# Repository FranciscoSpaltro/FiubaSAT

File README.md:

# Comunicación I2C

### Conexiones para la prueba con Arduino Nano

    1. GND (STM32) ---> GND (NANO)
    2. 5V  (STM32) ---> R_PULL_UP1 y R_PULL_UP2
    3. PB6 (STM32) ---> R_PULL_UP1 ---> PA5 (NANO) [SCL]
    4. PB7 (STM32) ---> R_PULL_UP2 ---> PA4 (NANO) [SDA]

### Protocolo para imprimir mensajes por Arduino via I2C
- Maestro (STM32): sin interrumpir la comunicación
    - Inicia la comunicación
    - Envía un comando a definir (IMPRIMIR_MENSAJE)
    - Envía la cadena caracteres sin interrumpir
    - Finaliza la comunicación
- Esclavo (ARDUINO):
    - Lee el comando
    - Recibe todos los bytes
    - Una vez finalizada la comunicacióon, imprime

### OBSERVACIONES
- FreeRTOS utiliza un contador de 32 bits para contar los ticks del sistema, lo que significa que se desbordará después de aproximadamente 49.7 días (para un sistema que corre a 1 ms por tick). Sin embargo, el cálculo de la diferencia, como en tu código, maneja correctamente el desbordamiento debido a la aritmética de enteros sin signo

### Próximos pasos
- Identificación de tipo de dato en el handshake? Vale la pena? El resto de los sensores no van a tener un micro
- Protección ante dirección de esclavo repetida
- Fallo en la conexión cableada se cuelga el I2C?
- En una falla que pasa con los mensajes que no se enviaron?
- Funciona bien la conexión entre hacer el rq (poner el mensaje en tx) y leer el dato (poner el mensaje en rx)? Es decir quien envia el dato puede trackear la respuesta?
- Investigar funcion i2c_write_restart de ve3wwg

- Tema memoria
- Si pido 5 bytes y me manda 1 que no se quede esperando después de un tiempo

### Comandos útiles RPi5
- pinout: muestra el pinout de la RPi
- gpiodetect: muestra los chips
- pinctrl: muestra info de todos los pines
- gpioinfo: muestra info de todos los pines por chip
- gpioget gpiochip0 4: muestra el estado del pin 4 del chip 0

### Tareas
- Rutina para chequeo de salud de los dispositivos
- Sacar los taskDelay, ver xTaskGetTickCount()
- ¿Mapa de esclavos por puerto? Y que decida por donde enviarlo (solo se necesitaría el slave_addr)

### Observaciones
- En los casos de reconexión/retransmisión, ver de combinar el taskYIELD() con un xTaskGetTickCount() para hacer que no vuelva a probar hasta que pase determinado tiempo
- Vale la pena las interrupciones?
- Revisar la variable global con la dirección del esclavo -> si hay más de un request como hago??
- La dirección 0x00 con el mensaje 0 está reservada para ERROR
- Función para leer?
- Revisar make_request, siempre hace get_i2c

### PROCESO DE TRANSMISION DE UN MENSAJE
1. Encolar un msg_t con la dirección y el dato a enviar en TXQ. El flag request debe estar en false
2. Iniciar la comunicación I2C en modo WRITE con i2c_start (puerto I2C, dirección del esclavo, false)
3. Enviar el byte de datos con i2c_write (puerto I2C, byte de datos)
4. Esperar a que se complete la transferencia de datos
5. Comprobar si se recibió ACK del esclavo
6. Enviar un STOP para finalizar la comunicación

### PROCESO DE SOLICITUD Y RECEPCIÓN DE UN MENSAJE
1. Encolar un msg_t con la dirección del esclavo en TXQ. El flag request debe estar en true
2. Iniciar la comunicación I2C en modo READ con i2c_start (puerto I2C, dirección del esclavo, true)
3. Leer el byte de datos con i2c_read (puerto I2C, true) y encolarlo en RXQ
4. Enviar un NACK si es el último byte a leer
5. Enviar un STOP para finalizar la comunicación

### FUNCIONES LIBOPENCM3
#### FUNCIONES DE CONFIGURACIÓN
1. i2c_peripheral_enable(uint32_t i2c): habilita el periférico I2C

2. i2c_peripheral_disable(uint32_t i2c): deshabilita el periférico I2C

3. i2c_set_own_7bit_slave_address(uint32_t i2c, uint8_t slave): configura la dirección de 7 bits para el periférico cuando está en modo esclavos

4. i2c_set_own_10bit_slave_address(uint32_t i2c, uint8_t slave): análogo pero para una dirección de 10 bits

5. i2c_enable_dual_addressing_mode(uint32_t i2c): habilita el modo de direccionamiento dual del periférico para permitir que el esclavo escuche dos direcciones

6. i2c_disable_dual_addressing_mode(uint32_t i2c): deshabilita el modo de direccionamiento dual

7. i2c_set_own_7_bit_slave_address_two(uint32_t i2c, uint8_t slave): configura una segunda dirección de esclavo de 7 bits

8. i2c_set_clock_frequency(uint32_t i2c, uint8_t freq): establece la frecuencia del reloj del periférico I2C en MHz

9. i2c_set_fast_mode(uint32_t i2c): configura el periférico para operar en modo rápido (hasta 400 kHz)

10. i2c_set_standard_mode(uint32_t i2c): configura el periférico para operar en modo estándar (hasta 100 kHz)

11. i2c_set_ccr(uint32_t i2c, uint16_t ccr): configura el valor del registro CCR (Clock Control Register) para controlar la velocidad de transmisión en el bus

12. i2c_set_trise(uint32_t i2c, uint8_t trise): establece el tiempo máximo de subida para la señal I2C (en ciclos de reloj)

13. i2c_set_dutycycle(uint32_t i2c, uint16_t dutycycle): configura el ciclo de trabajo del reloj I2C en modo rápido

14. i2c_enable_interrupt(uint32_t i2c, uint32_t interrupts): habilita interrupciones específicas para el periférico

15. i2c_disable_interrupt(uint32_t i2c, uint32_t interrupts): deshabilita interrupciones específicas para el periférico

16. i2c_enable_ack(uint32_t i2c): habilita la generación de señales de reconocimiento en respuesta a la recepción de datos

17. i2c_disable_ack(uint32_t i2c): deshabilita la generación de señales ACK, de modo que no se reconozcan las transmisioines entrantes. Se utiliza cuando se necesita ignorar las transmisiones o enviar una señal de NACK

18. i2c_enable_dma(uint32_t i2c): habilita el uso de DMA (Direct Memory Access) para las transmisiones I2C, lo que permite la transferencia automática de datos sin intervención del procesador (se utiliza cuando hay que realizar transferencias grandes de datos con mayor eficiencia)

19. i2c_disable_dma(uint32_t i2c): deshabilita el uso de DMA para las transmisiones I2C

20. i2c_set_speed(uint32_t i2c, uint32_t clock, uint32_t speed): configura la velocidad del bus I2C según la frecuencia de entrada y la velocidad de transferencia deseada (estándar o rápido)

#### FUNCIONES OPERATIVAS

1. i2c_send_start(uint32_t i2c): envia una condicion de inicio a los esclavos

2. i2c_get_data(uint32_t i2c): recupera un byte de datos del registro de datos

3. i2c_send_data(uint32_t i2c, uint8_t data): envía un byte de datos a través del bus I2C

4. i2c_send_stop(uint32_t i2c): envia una condicion de parada en el bus I2C

5. i2c_clear_stop(uint32_t i2c): borra la señal de STOP, permitiendo que el periférico vuelva a un estado donde pueda iniciar nuevas operaciones de transmisión

6. i2c_nack_next(uint32_t i2c): envía un NACK después del próximo byte recibido. Se utiliza cuando el maestro no necesita más datos del esclavo y quiere terminar la comunicación

7. i2c_nack_current(uint32_t i2c): envía un NACK  inmediatamente después de recibir el byte actual para finalizar la recepción de datos

8. i2c_set_dma_last_transfer(uint32_t i2c): indica que la próxima transmisión será la úlitma en una secuencia de transferencias DMA

9. i2c_clear_dma_last_transfer(uint32_t i2c): borra el flag que indica la última transferencia DMA

10. [STATIC] i2c_read7_v1(uint32_t i2c, uint8_t addr, uint8_t *buf, size_t len): realiza una lectura desde un dispositivo esclavo de 7 bits y almacena los datos en el buffer proporcionado

11. [STATIC] i2c_write_7_v1(uint32_t i2c, uint8_t addr, const uint8_t data, size_t length): envía una secuencia de datos al dispositivo esclavo de direccion de 7 bits en el bus I2C

12. i2c_transfer7(uint32_t i2c, uint8_t addr, const uint8_t *w, size_t wn, uint8_t *r, size_t rn): realiza una transacción completa I2C de 7 bits con escritura y lectura (si corresponde). Se envía datos y luego se reciben en la misma transacción

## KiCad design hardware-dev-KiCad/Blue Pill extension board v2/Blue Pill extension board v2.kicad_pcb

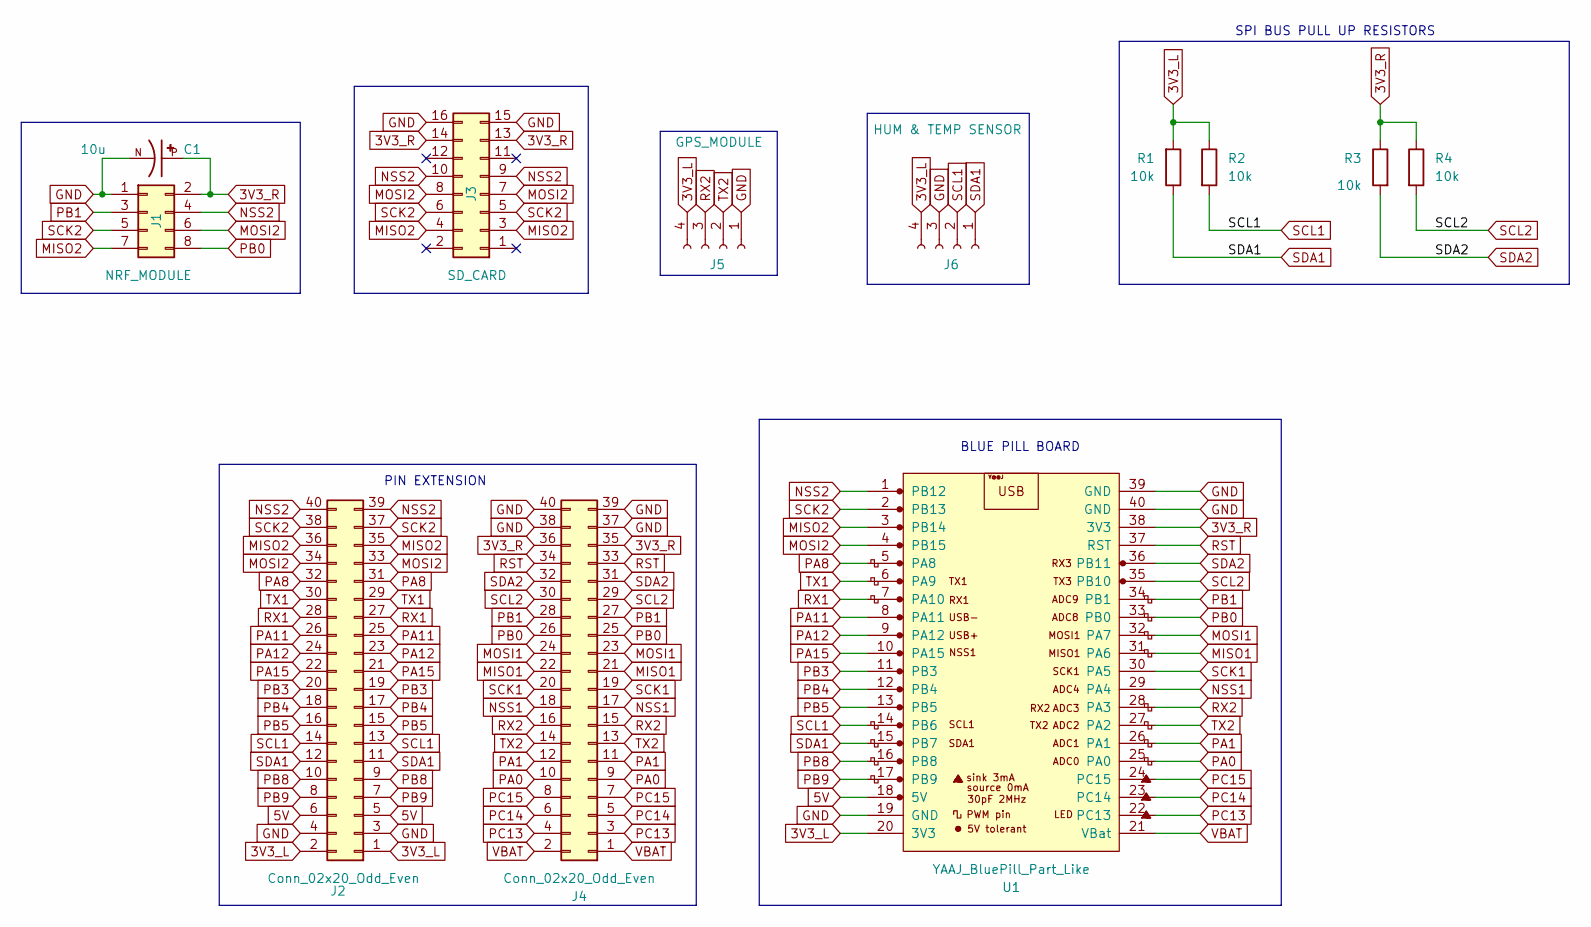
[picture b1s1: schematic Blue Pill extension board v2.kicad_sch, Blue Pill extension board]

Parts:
C1: 10u; CAPPRD250W50D500H1100; PARTREV 20-DEC-19
J1: NRF_MODULE; PinSocket_2x04_P2.54mm_Vertical
J2, J4: Conn_02x20_Odd_Even; PinSocket_2x20_P2.54mm_Vertical
J3: SD_CARD; PinSocket_2x08_P2.54mm_Vertical
J5: GPS_MODULE; PinSocket_1x04_P2.54mm_Vertical
J6: HUM & TEMP SENSOR; PinSocket_1x04_P2.54mm_Vertical
R1, R2, R3, R4: 10k; R_Axial_DIN0207_L6.3mm_D2.5mm_P7.62mm_Horizontal
U1: YAAJ_BluePill_Part_Like; BluePill_modified(F.Courtyard)

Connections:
3V3_L: J2.1, J2.2, J5.4, J6.4, R1.2, R2.1, U1.20 (3V3)
3V3_R: C1.P, J1.2, J3.13, J3.14, J4.35, J4.36, R3.1, R4.1, U1.38 (3V3)
5V: J2.5, J2.6, U1.18 (5V)
GND: C1.N, J1.1, J2.3, J2.4, J3.15, J3.16, J4.37, J4.38, J4.39, J4.40, J5.1, J6.3, U1.19 (GND), U1.39 (GND), U1.40 (GND)
MISO1: J4.21, J4.22, U1.31 (PA6)
MISO2: J1.7, J2.35, J2.36, J3.3, J3.4, U1.3 (PB14)
MOSI1: J4.23, J4.24, U1.32 (PA7)
MOSI2: J1.6, J2.33, J2.34, J3.7, J3.8, U1.4 (PB15)
NSS1: J4.17, J4.18, U1.29 (PA4)
NSS2: J1.4, J2.39, J2.40, J3.9, J3.10, U1.1 (PB12)
PA0: J4.9, J4.10, U1.25 (PA0)
PA1: J4.11, J4.12, U1.26 (PA1)
PA8: J2.31, J2.32, U1.5 (PA8)
PA11: J2.25, J2.26, U1.8 (PA11)
PA12: J2.23, J2.24, U1.9 (PA12)
PA15: J2.21, J2.22, U1.10 (PA15)
PB0: J1.8, J4.25, J4.26, U1.33 (PB0)
PB1: J1.3, J4.27, J4.28, U1.34 (PB1)
PB3: J2.19, J2.20, U1.11 (PB3)
PB4: J2.17, J2.18, U1.12 (PB4)
PB5: J2.15, J2.16, U1.13 (PB5)
PB8: J2.9, J2.10, U1.16 (PB8)
PB9: J2.7, J2.8, U1.17 (PB9)
PC13: J4.3, J4.4, U1.22 (PC13)
PC14: J4.5, J4.6, U1.23 (PC14)
PC15: J4.7, J4.8, U1.24 (PC15)
RST: J4.33, J4.34, U1.37 (RST)
RX1: J2.27, J2.28, U1.7 (PA10)
RX2: J4.15, J4.16, J5.3, U1.28 (PA3)
SCK1: J4.19, J4.20, U1.30 (PA5)
SCK2: J1.5, J2.37, J2.38, J3.5, J3.6, U1.2 (PB13)
SCL1: J2.13, J2.14, J6.2, R2.2, U1.14 (PB6)
SCL2: J4.29, J4.30, R4.2, U1.35 (PB10)
SDA1: J2.11, J2.12, J6.1, R1.1, U1.15 (PB7)
SDA2: J4.31, J4.32, R3.2, U1.36 (PB11)
TX1: J2.29, J2.30, U1.6 (PA9)
TX2: J4.13, J4.14, J5.2, U1.27 (PA2)
VBAT: J4.1, J4.2, U1.21 (VBat)

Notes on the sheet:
BLUE PILL BOARD
SPI BUS PULL UP RESISTORS
PIN EXTENSION

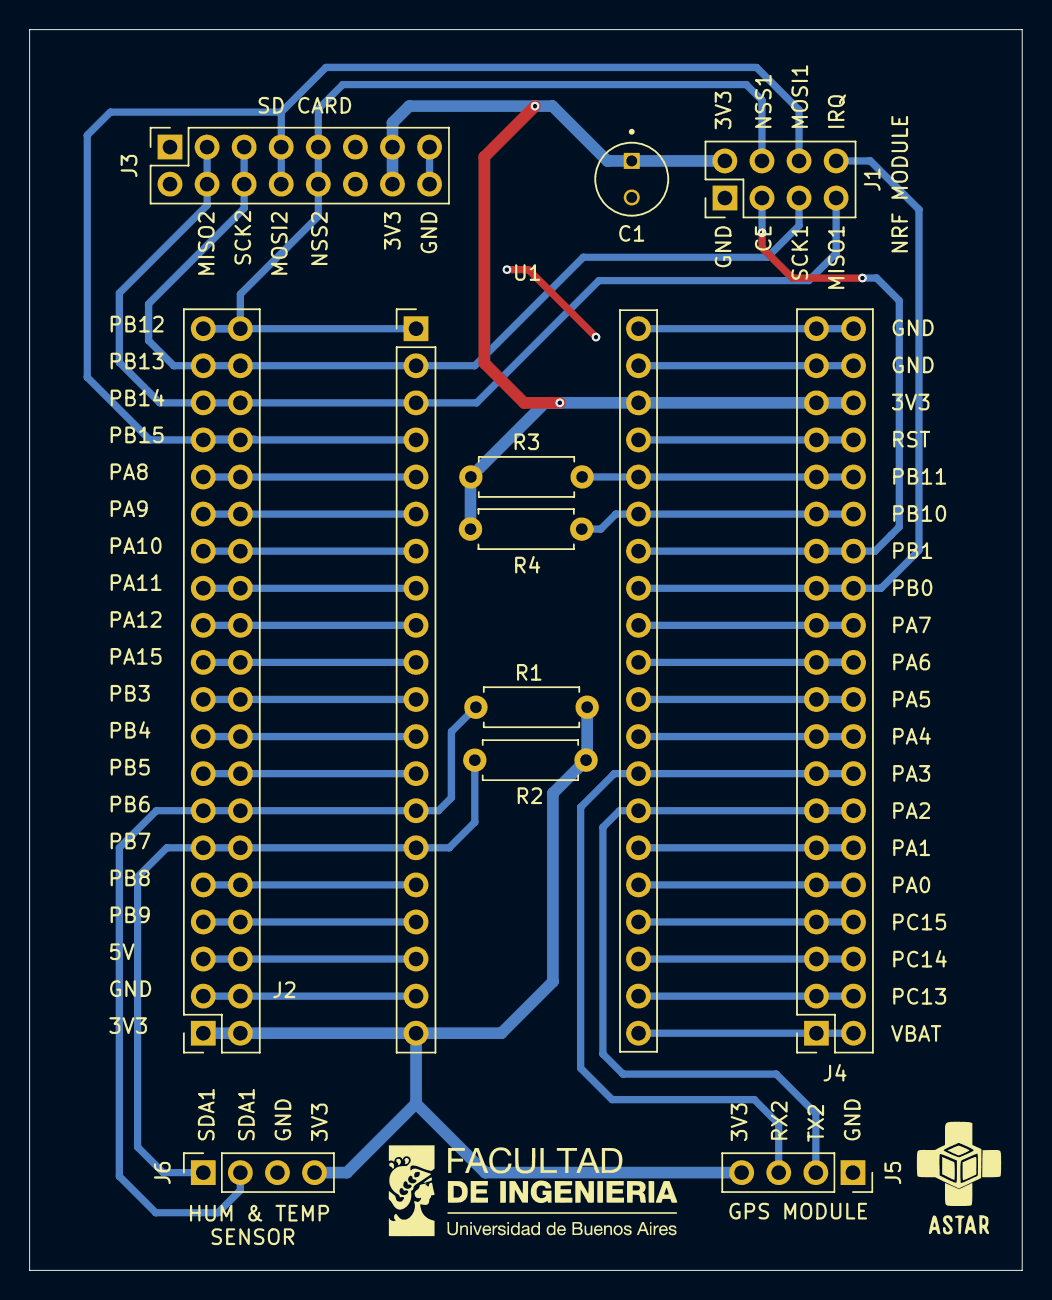
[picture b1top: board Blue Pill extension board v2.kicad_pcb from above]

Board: 2 copper layers, 68.0 x 85.0 mm, 12 parts (0 on the bottom side), 38 nets.

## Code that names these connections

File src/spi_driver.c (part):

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            gpio_set_mode(GPIOA,
                GPIO_MODE_OUTPUT_50_MHZ,
                GPIO_CNF_OUTPUT_ALTFN_PUSHPULL,
                GPIO4 | GPIO5 | GPIO7);  // NSS=PA4, SCK=PA5, MOSI=PA7

            gpio_set_mode(GPIOA,
                GPIO_MODE_INPUT,
                GPIO_CNF_INPUT_FLOAT,
                GPIO6);  // MISO=PA6

            spi_slaves_init(spi->slaves);
        }
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            gpio_set_mode(GPIOA,
                GPIO_MODE_INPUT,
                GPIO_CNF_INPUT_FLOAT,
                GPIO4 | GPIO5 | GPIO7);  // NSS=PA4, SCK=PA5, MOSI=PA7

            gpio_set_mode(GPIOA,
                GPIO_MODE_OUTPUT_50_MHZ,
                GPIO_CNF_OUTPUT_ALTFN_PUSHPULL,
                GPIO6);  // MISO=PA6

            spi_set_slave_mode(SPI1);

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                GPIOB,
                GPIO_MODE_OUTPUT_50_MHZ,
                GPIO_CNF_OUTPUT_ALTFN_PUSHPULL,
                GPIO12 | GPIO13 | GPIO15 // PB12=NSS2 PB13=SCK2 PB15=MOSI2 
            );

            gpio_set_mode(
                GPIOB,
                GPIO_MODE_INPUT,
                GPIO_CNF_INPUT_FLOAT,
                GPIO14 // MISO2=PB14
            );
            spi_slaves_init(spi->slaves);
        }
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                GPIOB,
                GPIO_MODE_INPUT,
                GPIO_CNF_INPUT_FLOAT,
                GPIO12 | GPIO13 | GPIO15 // PB12=NSS2 PB13=SCK2 PB15=MOSI2 
            );

            gpio_set_mode(
                GPIOB,
                GPIO_MODE_OUTPUT_50_MHZ,
                GPIO_CNF_OUTPUT_ALTFN_PUSHPULL,
                GPIO14 // MISO2=PB14
            );
            spi_set_slave_mode(SPI2);

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
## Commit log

2024-04-11 Prueba blink
2024-04-12 Creación de directorio Prueba Blink
2024-04-12 Prueba USART
2024-04-23 Aprendiendo STM32
2024-04-25 Commit main
2024-04-26 Modularizacion UART y Blink
2024-04-27 Prueba timer. Borrador mutex y semaforo
2024-04-27 Semaforo UART. Sigue sin andar UART_rcv
2024-04-28 Funciona provisorio UART rcv
2024-04-29 Arreglos UART rcv
2024-05-03 Reorganización y pruebas locales
2024-05-05 cambios UART
2024-05-05 solo repo global
2024-05-05 update facu
2024-06-14 Recibe por UART1 -> envia por UART1
2024-08-19 Manual para la instalación y configuración inicial de Docker
2024-08-19 Acondicionamiento de la rama test_branch para el merge
2024-08-19 Acondicionamiento de la rama main para comenzar el proyecto
2024-08-19 Manual para inicializar Docker
2024-08-19 Eliminamos archivos innecesarios del merge
2024-08-19 Estandarización UARTs y cambio frecuencia blink
2024-08-20 Subo el driver para compartir USB junto al instructivo
2024-08-20 archivos del manual para grabar desde Docker
2024-08-20 receive por interrupcion
2024-08-20 test UART1
2024-08-21 Modificaciones a los apuntes de Docker
2024-08-21 Driver para ST-LINK V2 (WIN)
2024-08-22 Comentarios en códigos de UART
2024-08-25 Agrego miniblink para testing
    Testear programación desde Docker
2024-08-25 Agrego archivo target de opencd para stm32f103
2024-08-26 Rename Grabar desde Docker.md to Cómo grabar STM32 desde Docker usando PlatformIO.md
2024-08-26 comentarios uart2
2024-08-26 Acomodo comentarios uart1
2024-08-26 Logica de buffer y estandarizacion de tipos de datos
2024-08-26 Buffer circular y prueba
2024-08-26 Agrego UART3 y lo llamo como print desde UARTx
2024-08-27 unificacion UARTs
2024-08-27 Contabilizacion interrupciones
2024-08-28 Saco buffer y trabajo con rxq
2024-08-28 Semaphore para monitoreo datos y taskReceive fuera de UART
2024-08-28 UART_receive devuelve Base_Type y recibe dato
2024-08-28 UART_receive con xTicksToWait dinamico
2024-08-29 Documentación y devolucion de BaseType_t
2024-09-01 Cambios previos makefile
2024-09-01 Compilación sin platformIO
2024-09-02 Corrección del Makefile para el clonado y compilación autom. de libopencm3
2024-09-02 Corrección archivo makefile libopencm3
2024-09-02 Archivos Docker
2024-09-02 Cambios en Dockerfile, ya no se necesita la funcion para grabar ni clonar libopencm3 por incluirse en el Makefile
2024-09-02 Modificaciones a los .bat de Docker para crear la carpeta app por fuera del repositorio
2024-09-02 Función GPS
2024-09-02 Prueba branch
2024-09-02 Prueaba branch
2024-09-02 Pruebo seguir trabajando en la rama independientemente de spi
2024-09-03 Primeros cambios en i2C (no funciona)
2024-09-04 feat: primeras pruebas de comunicacion i2c con Arduino
2024-09-04 doc: agrego las conexiones al README
2024-09-04 refactor: modificacion a los .bat de Docker para que el USB se comparta y adjunte automaticamente
2024-09-04 refactor: agrego el script attach_usb para automatizar la asoacion del ST-Link al Docker
2024-09-04 doc: adecuo los apuntes para automatizar la asociacion del usb
2024-09-04 refactor: implemento los cambios de scripts para Docker de la rama main
2024-09-05 refactor: agrego el comando andflash en el Makefile y fuerzo el reinicio del microcontrolador
2024-09-06 code: cambios en el programa de Arduino
2024-09-06 directory: carpeta ino
2024-09-06 refactor: uso mutex para i2c y cambio a taskYELD para el wait
2024-09-07 feat: agrego funcion de transmision y recepcion
2024-09-07 Inclusion de spi_driver
2024-09-07 fix: intellisense
2024-09-07 code: avance en implementacion i2c1, escribe correctamente. Observaciones en RDME
2024-09-07 doc: actualizo las tareas y comentarios del RDME
2024-09-07 code: implementacion i2c2 en un script aparte
2024-09-07 code: codigo para arduino uno con slave 0x04
2024-09-08 doc: Create Solucionar subrayado en VSC.md
2024-09-08 Vuelvo a la version separada
2024-09-08 code: cambios en los scripts de Arduino p I2C
2024-09-08 Elimino .c y cambio pruebas en el main
2024-09-08 code: funciona el i2c_unif pero mantengo todos los archivos, los borro en el prox commit
2024-09-08 code: comienzo de codigo para recepcion
2024-09-08 code: cambios en encabezados
2024-09-09 feat: implementacion de la recepcion con semaforos
2024-09-09 code: modificacion scripts Arduino para HC-SR04
2024-09-09 doc: actualizacion de notas en el readme
2024-09-09 refactor: direccion de esclavo global para independizar rq
2024-09-09 refactor: intento de reconexion ante falla
2024-09-10 refactor UART
    add circular_buffer for rxq and its auxiliar functions
    add documentation
    change ISR
2024-09-10 feat testGPS
2024-09-10 creation NMEA for GPS
    NMEA for GPS decode and struct definition
2024-09-10 Delete src/NMEA.h
    switch directory to inc
2024-09-10 Delete src/test.h
    switch directory to inc
2024-09-10 Delete src/uart.h
    switch directory to inc
2024-09-10 feat main for GPS task & test
2024-09-10 creation of circular_buffer_t
    used for rxq in UART
2024-09-10 feat .h UART 2.0
2024-09-11 add files and -lm flag
2024-09-11 rm testing UART1/2 by echo
2024-09-11 uart 2.0 sin platformio
2024-09-12 Back-up LCD
2024-09-12 feat: agrego estructura spi_t y adapto funciones
2024-09-17 code: Re-codificion de I2C, se optimiza para I2C1, debe generalizarse
2024-09-17 refactor: cambio nombre y ubicacion de archivos
2024-09-17 doc: documentacion de las funciones de i2c manteniendo el estilo de uart
2024-09-18 feat: cambio de funcionalidades
2024-09-19 refactor: remodularizacion, cambio funciones static, paso los puertos por parametro
2024-09-19 doc: pasos a seguir y observaciones
2024-09-21 refactor: request de mas de un byte
2024-09-22 docs: apuntes a seguir
2024-09-23 code: Lectura de htu21d y envio de datos a Arduino - i2c
2024-09-23 code: lectura htu21d por arduino nano
2024-09-23 log: subo archivos correspondientes al commit anterior
2024-09-30 feat: drivers basicos del modulo NRF24l01 funcionando
2024-09-30 feat: estructura para seleccion de slaves
2024-10-02 Feat: agrego funciones spi_transmit_receive y spi_receive (No estan testeadas)
2024-10-02 refactor: cambios en el envio de mensajes, cola response, funcion print_i2c para Arduino con 0x04
2024-10-05 ajustes tests uart
2024-10-05 refactor: agrego algunos prints de debug y pongo un timeout para la escritura
2024-10-06 Avance pruebas uart
2024-10-06 refactor: agrego timeout en las funciones de espera + codigo arduino uno para reset (pruebas)
2024-10-06 pruebas uart y gps
2024-10-06 Agrego handle para vTaskDelete
2024-10-06 code: agrego pruebas del bus con Arduino UNO
2024-10-10 fix: SPI2 setup fixed
2024-10-10 feat: nuevos archivos para la sd memory
2024-10-10 fix: soluciono el problema al desconectar un sensor y modularizo los archivos en driver htu21d + driver i2c + pruebas
2024-10-10 feat: cambio del tipo de puntero data y modificacion de la logica necesaria
2024-10-10 add Test mode
2024-10-10 docs: agrego comentarios a las funciones
2024-10-10 modificaciones en los archivos
2024-10-16 docs: manual para abrir Docker en Raspi
2024-10-16 code: cambio la implementacion de i2c, elimino cola responses y paso un puntero
2024-10-17 refactor: modificaciones pendientes en .h
2024-10-17 docs: habilitacion i2c en raspi
2024-10-17 code: inicio de entorno de testing
2024-10-19 code: linea de vida para testing en la RPi
2024-10-19 fix: contexto
2024-10-21 code: testing con raspi y analizador logico
2024-10-21 Otros commits que no se agregaron
2024-10-23 code: uso del timer 2 - cuenta PERIOD_INTERRUPT segundos pero falla en la primera ejecucion
2024-10-23 feat: desarrollo de conexiones basicas del shield (DRC OK)
2024-10-23 Elimino archivos de backup y librerias sin uso
2024-10-23 code: implementacion de 3 modos de testeo: echo, letra i2c y mensajes largos i2c
2024-10-23 code: codigo de testeo para RPi5
2024-10-26 doc: cambios en la isntalacion de docker para RPi 64 bits
2024-11-07 feat: adaptacion de drivers sd con FreeRtos
2024-11-07 Funciones para manejo de archivos
2024-11-07 Cambios de routeo y añado PCB para funcionar sin PTH
2024-12-18 Modifico placa para hacerla de una sola capa
2024-12-23 Agrego comentarios y reestructuro carpetas
2024-12-27 Cambio numero de esclavo
2024-12-27 Cambio a SPI2 y a SLAVE1, agrego print en caso de error al seleccionar el slave
2024-12-27 Cambio include ../
2024-12-27 Modifico para poder compilar las carpetas
